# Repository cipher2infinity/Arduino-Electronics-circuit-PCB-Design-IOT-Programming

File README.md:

# Arduino : Electronics circuit, PCB Design & IOT Programming

You can check the course curriculum on our [WEBSITE](https://www.cipher2infinity.com/)

## Content
* Images of Datalogger
* Hardware design files and firmware files for Industrial DataLogger.
* Examples codes used in demos of all the sections of datalogger.
* hardware descreption section includes descreptions for all the hardware blocks of datalogger. 
* Libraries used in demo code

## Introduction
Please check the following links for demostration of Datalogger

1. This [video](https://drive.google.com/open?id=1AglGJTn_O3K_O5rFmPPeSSnq5-zFRN2F) describes the entire PCB of Industrial Datalogger

2. This [video](https://drive.google.com/open?id=1-QjOal9vDFr6C30vdyRp-lrAA95-3nSr) gives the demostration of each and every inetrface of Industrial Datalogger

## Features
* SMPS (5V)
* LDO Regulator (3.3v)
* Relay Driver										 (2 CH)
* DC Motor Speed Controller
* 0-10 V Digital Input 					 (4 CH)
* 0-10 V Analog Input 						 (4 CH)
* 4-20 mA Receiver								 (2 CH)
* Real Time Clock
* Bluetooth Low Energy 
* WiFi Module
* SD Card Module
* RS232 Interface
* RS485 Interface
* 6 Pin ICSP Headers
* Serial Programming using UART0

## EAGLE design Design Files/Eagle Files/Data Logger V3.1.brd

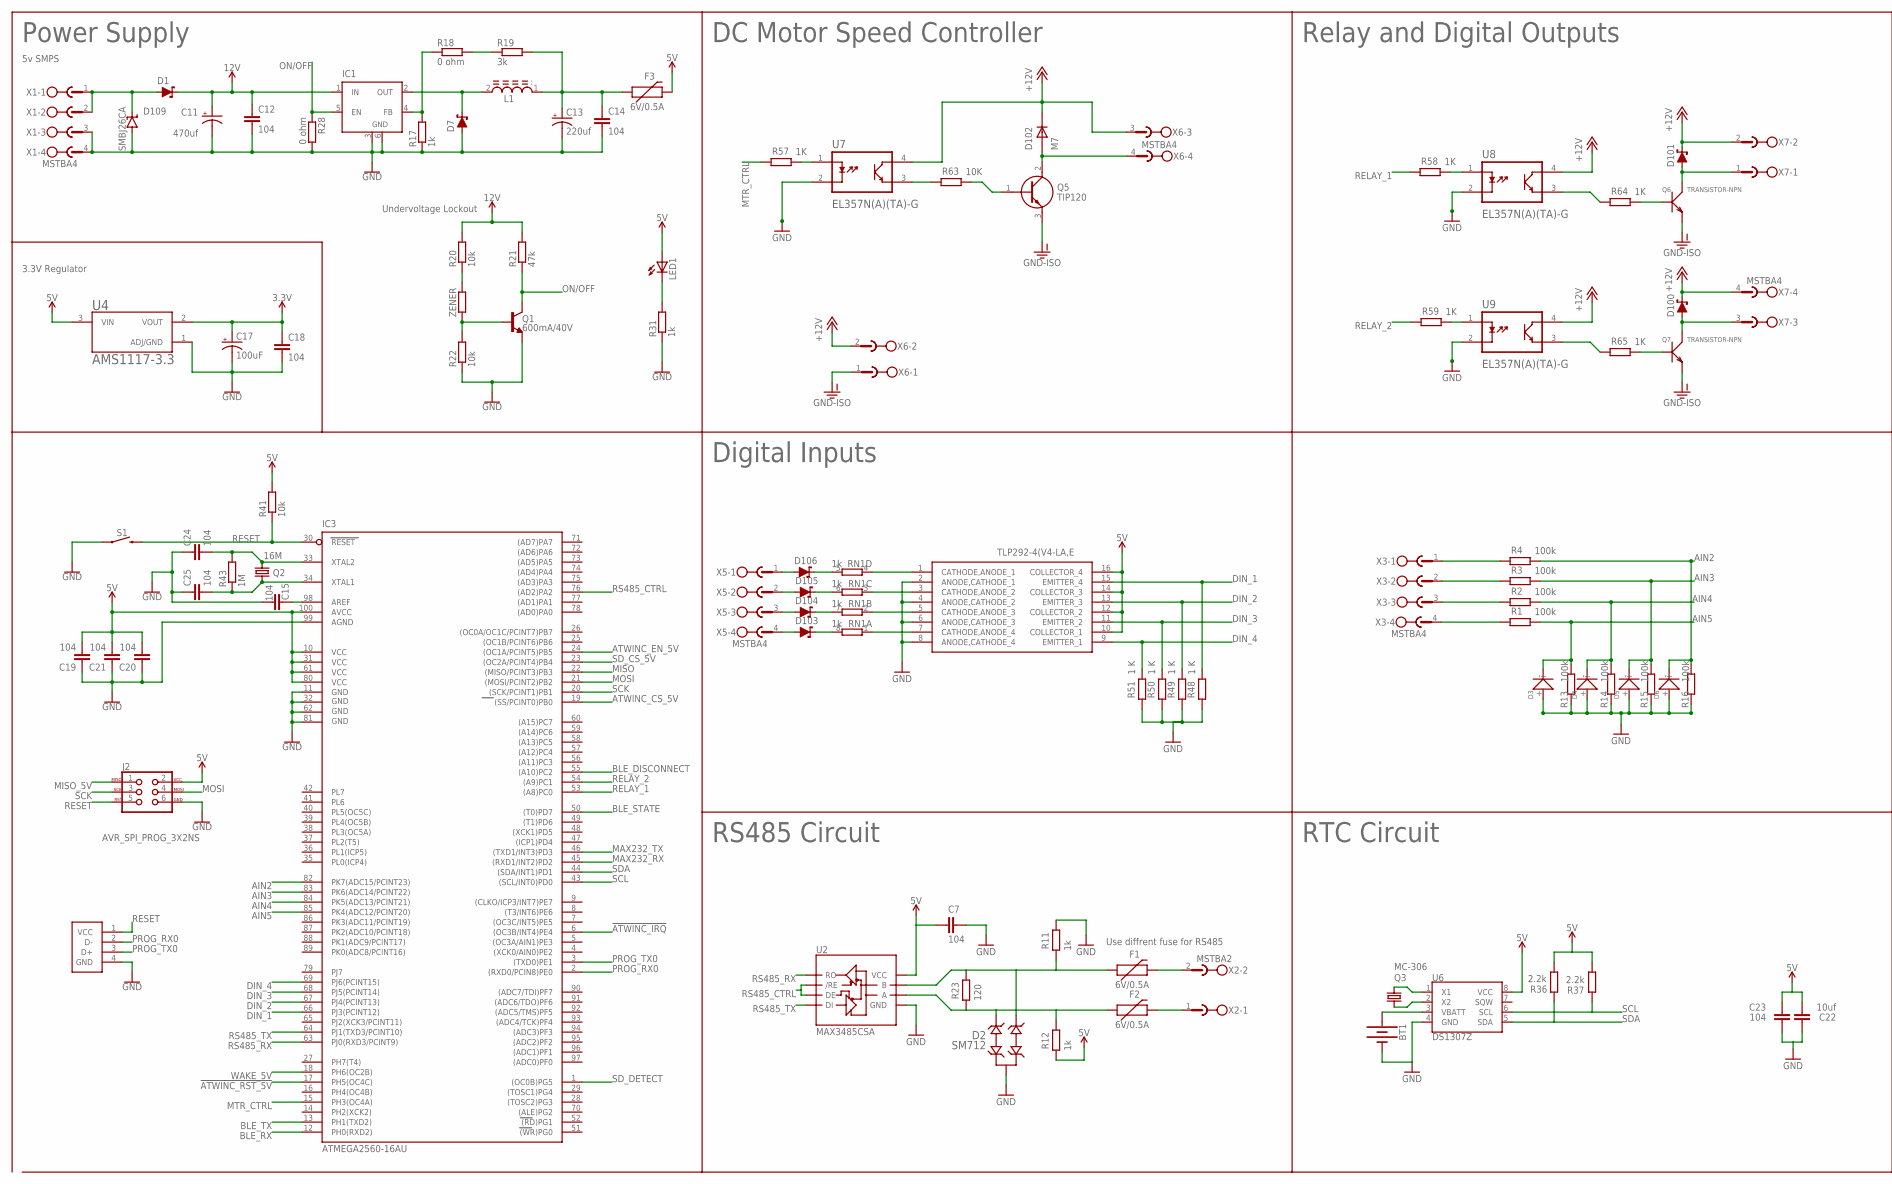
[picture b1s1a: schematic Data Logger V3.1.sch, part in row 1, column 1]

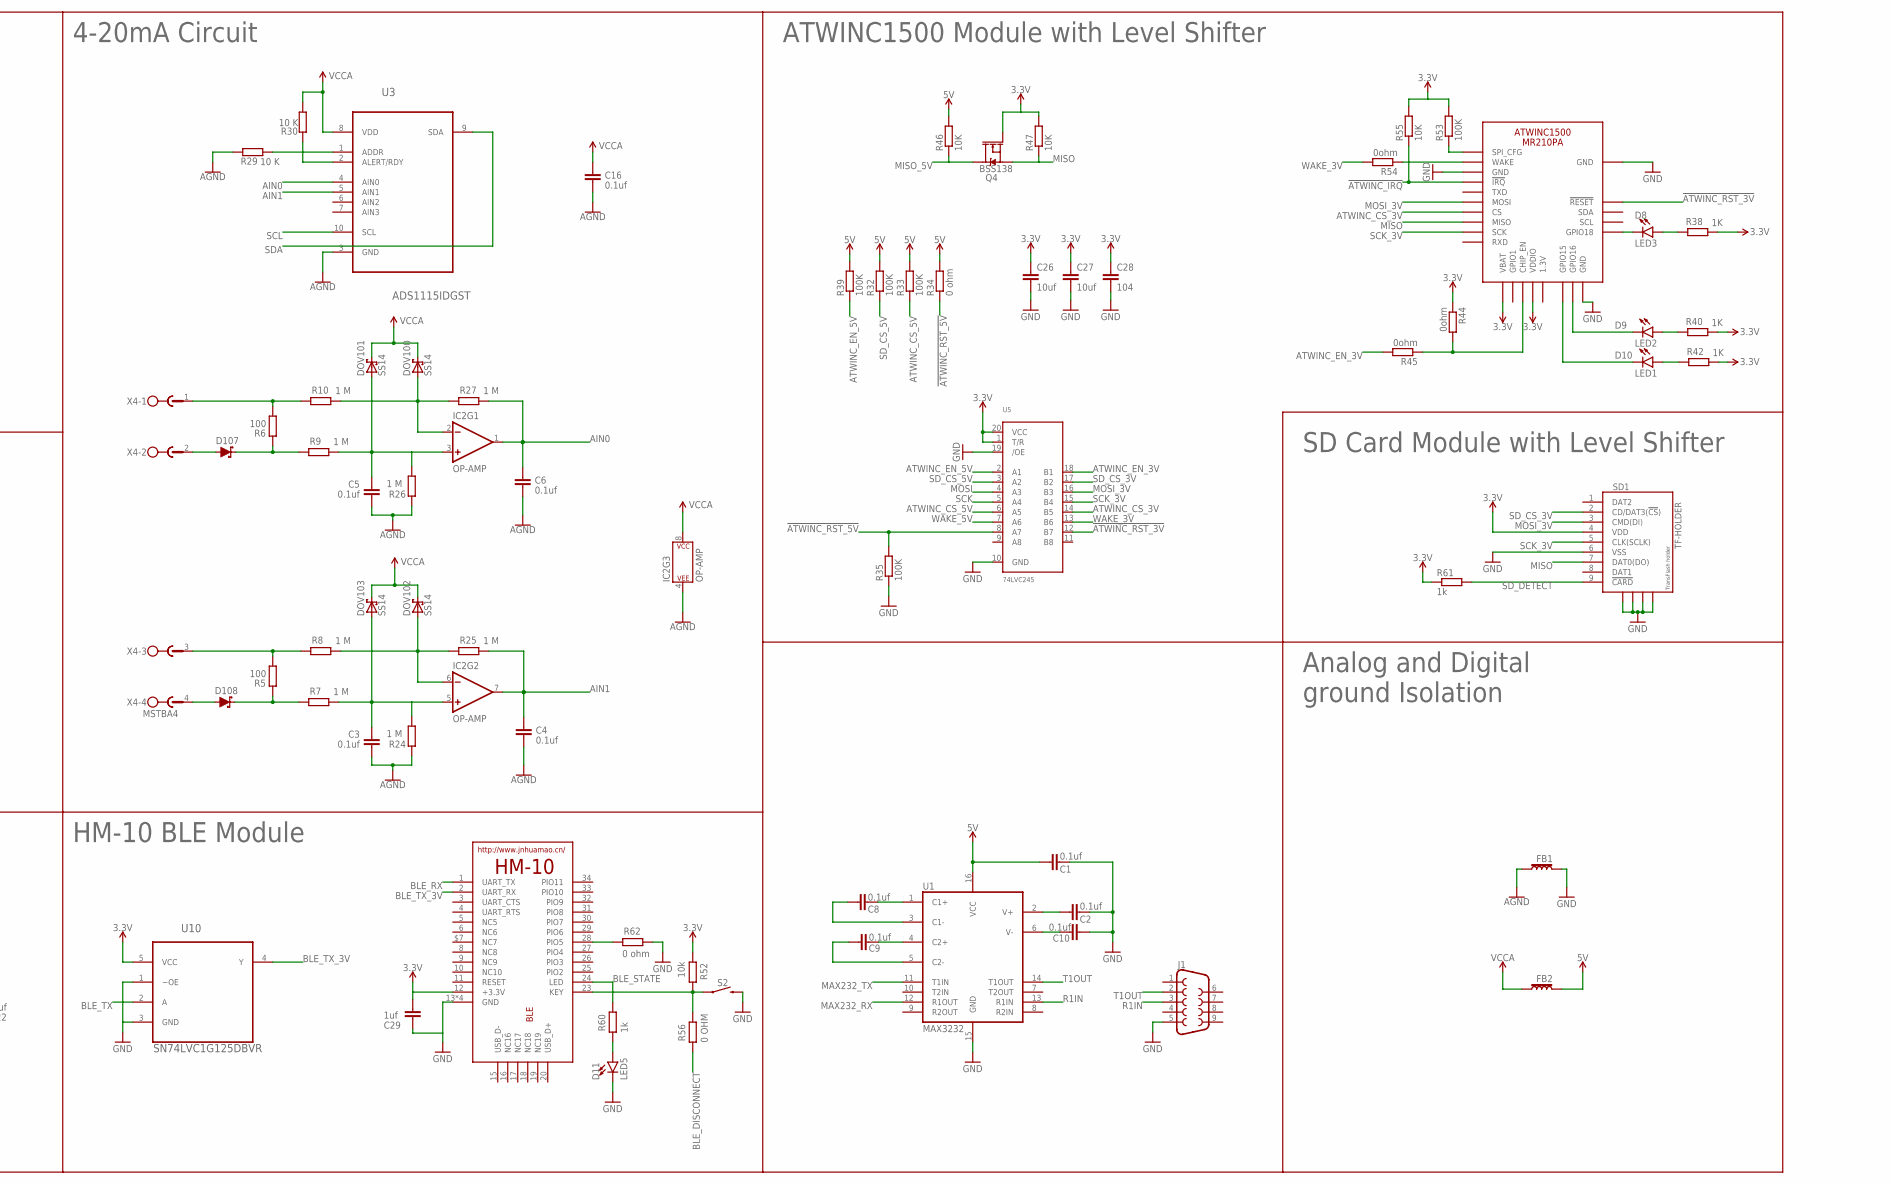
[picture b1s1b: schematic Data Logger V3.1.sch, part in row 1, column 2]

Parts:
BLE: HM-10-BOARD; 26.9X13X2.2_BOARD
BT1: BATTERY-20MM_PTH; BATTCOM_20MM_PTH
C1, C2, C3, C4, C5, C6, C8, C9, C10, C16: 0.1uf; C0805
C7, C12, C14, C15, C18, C19, C20, C21, C23, C24, C25, C28: 104; C0805
C11: 470uf; E5-8,5
C13: 220uf; 150CLZ-1014
C17: 100uF; PANASONIC_D
C22, C26, C27: 10uf; C0805
C29: 1uf; C0805
D1, D7, D100, D101, D103, D104, D105, D106, D107, D108: 3A/40V/500mV; SMA-DIODE
D2: SM712; SOT-23-3
D3, D4, D5, D6: SMD-DIODE-ZENER-5.1V-500MW(SOD-123); SOD-123
D8: LED3; LED-0603
D9: LED2; LED-0603
D10: LED1; LED-0603
D11: LED5; LED-0603
D102: M7; DIOM505270X240
D109: SMBJ26CA; SMBJ
DOV100, DOV101, DOV102, DOV103: SS14; DO-214AC
F1, F2, F3: 6V/0.5A; 1206
FB1, FB2: 30Ω/1.8A; 0603
IC1: LM2596S; TO263-5
IC2: OP-AMP; SO08
IC3: ATMEGA2560-16AU; TQFP100
IC4: TLP292-4(V4-LA,E; SOIC127P700X230-16N
J1: DB9MALE; DB9_MALE
J2: AVR_SPI_PROG_3X2NS; 2X3-NS
L1: SRR1260-680M; INDP125125X600N
LED1: LEDCHIP-LED0805; CHIP-LED0805
PROG: 61400416121
Q1: 600mA/40V; SOT23-3
Q2: 16M; HC49US
Q3: MC-306
Q4: BSS138; SOT23-3
Q5: TIP120; TO220
Q6, Q7: TRANSISTOR-NPN; SOT-23
R1, R2, R3, R4, R13, R14, R15, R16: 100k; R0805
R5, R6: 100; R0805
R7, R8, R9, R10, R24, R25, R26, R27: 1 M; R0805
R11, R12, R17, R31, R60, R61: 1k; R0805
R18, R28, R34, R62: 0 ohm; R0805
R19: 3k; R0805
R20, R22, R41, R52: 10k; R0805
R21: 47k; R0805
R23: 120; R0805
R29, R30: 10 K; R0805
R32, R33, R35, R39, R53: 100K; R0805
R36, R37: 2.2k; R0805
R38, R40, R42, R57, R58, R59, R64, R65: 1K; R0805
R43: 1M; R0805
R44, R45, R54: 0ohm; R0805
R46, R47, R55, R63: 10K; R0805
R48, R49, R50, R51: 1 K; R0805
R56: 0 OHM; R0805
RN1: 1k; CAY16
S1, S2: MOMENTARY-SWITCH-SPST-SMD-6.0X3.5MM; TACTILE_SWITCH_SMD_6.0X3.5MM
SD1: TF-HOLDER; TF-PULL
U1: MAX3232; SO16
U2: MAX3485CSA; SO08
U3: ADS1115IDGST; SOP50P490X110-10N
U4: AMS1117-3.3; SOT229P700X180-4N
U5: 74LVC245; TSSOP20
U6: DS1307Z; SO08-0.15
U7, U8, U9: EL357N(A)(TA)-G; SOP254P700X200-4N
U10: SN74LVC1G125DBVR; SOT95P280X145-5N
WIFI: ATWINC1500_MR210PB; ATWINC1500_MR210PA
X1, X3, X4, X5, X6, X7: MSTBA4
X2: MSTBA2
ZENER: R0204/7; 0204/7

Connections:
3.3V: BLE.12 (+3.3V), C17.+, C18.1, C26.1, C27.1, C28.1, C29.2, Q4.1 (G), R38.1, R40.1, R42.1, R44.1, R47.2, R52.2, R53.2, R55.2, R61.1, SD1.4 (VDD), U4.2 (VOUT), U5.1 (T/R), U5.20 (VCC), U10.5 (VCC), WIFI.J20 (VBAT), WIFI.J23 (VDDIO)
5V: C1.2, C7.1, C19.2, C20.2, C21.2, C22.2, C23.2, F3.2, FB2.2, IC3.10 (VCC), IC3.31 (VCC1), IC3.61 (VCC2), IC3.80 (VCC3), IC3.100 (AVCC), IC4.10 (COLLECTOR_1), IC4.12 (COLLECTOR_2), IC4.14 (COLLECTOR_3), IC4.16 (COLLECTOR_4), J2.2, LED1.A, R12.2, R32.2, R33.2, R34.2, R36.1, R37.1, R39.2, R41.2, R46.2, U1.16 (VCC), U2.8 (VCC), U4.3 (VIN), U6.8 (VCC)
12V: C11.+, C12.1, D1.C, IC1.1 (IN), R20.2, R21.2
!ATWINC_IRQ: IC3.6 ((OC3B/INT4)PE4), R55.1, WIFI.J13 (!IRQ)
!ATWINC_RST_3V: U5.12 (B7), WIFI.J4 (!RESET)
!ATWINC_RST_5V: IC3.17 (PH5(OC4C)), R34.1, R35.2, U5.8 (A7)
+12V: D100.C, D101.C, D102.C, U7.4 (C), U8.4 (C), U9.4 (C), X6.2, X6.3, X7.2, X7.4
AGND: C3.1, C4.1, C5.1, C6.1, C16.1, FB1.1, IC2.4 (P$V-), R24.2, R26.2, R29.1, U3.3 (GND)
AIN0: C6.2, IC2.1 (OUT), R27.1, U3.4 (AIN0)
AIN1: C4.2, IC2.7 (OUT), R25.1, U3.5 (AIN1)
AIN2: D6.-, IC3.82 (PK7(ADC15/PCINT23)), R4.1, R16.1
AIN3: D5.-, IC3.83 (PK6(ADC14/PCINT22)), R3.1, R15.1
AIN4: D4.-, IC3.84 (PK5(ADC13/PCINT21)), R2.1, R14.1
AIN5: D3.-, IC3.85 (PK4(ADC12/PCINT20)), R1.1, R13.1
AREF: C15.1, IC3.98 (AREF)
ATWINC_CS_3V: U5.14 (B5), WIFI.J16 (CS)
ATWINC_CS_5V: IC3.19 ((SS/PCINT0)PB0), R33.1, U5.6 (A5)
ATWINC_EN_3V: R45.2, U5.18 (B1)
ATWINC_EN_5V: IC3.24 ((OC1A/PCINT5)PB5), R39.1, U5.2 (A1)
BLE_DISCONNECT: IC3.55 ((A10)PC2), R56.2
BLE_RX: BLE.1 (UART_TX), IC3.12 (PH0(RXD2))
BLE_STATE: BLE.24 (LED), IC3.50 ((T0)PD7), R60.1
BLE_TX: IC3.13 (PH1(TXD2)), U10.2 (A)
BLE_TX_3V: BLE.2 (UART_RX), U10.4 (Y)
DIN_1: IC3.66 (PJ3(PCINT12)), IC4.15 (EMITTER_4), R48.1
DIN_2: IC3.67 (PJ4(PCINT13)), IC4.13 (EMITTER_3), R49.1
DIN_3: IC3.68 (PJ5(PCINT14)), IC4.11 (EMITTER_2), R50.1
DIN_4: IC3.69 (PJ6(PCINT15)), IC4.9 (EMITTER_1), R51.1
GND: BLE.13 (GND), BLE.14 (GND), BLE.21 (GND), BLE.22 (GND), BT1.2 (-), C1.1, C2.1, C7.2, C10.1, C11.-, C12.2, C13.-, C14.2, C15.2, C17.-, C18.2, C19.1, C20.1, C21.1, C22.1, C23.1, C24.1, C25.1, C26.2, C27.2, C28.2, C29.1, D2.3 (GND), D3.+, D4.+, D5.+, D6.+, D7.A, D11.C, D109.A, FB1.2, IC1.3 (GND), IC1.6 (GND), IC3.11 (GND), IC3.32 (GND1), IC3.62 (GND2), IC3.81 (GND3), IC3.99 (AGND), IC4.2 (ANODE,CATHODE_1), IC4.4 (ANODE,CATHODE_2), IC4.6 (ANODE,CATHODE_3), IC4.8 (ANODE,CATHODE_4), J1.5, J2.6, PROG.4 (GND), Q1.2 (E), R11.1, R13.2, R14.2, R15.2, R16.2, R17.1, R22.1, R28.2, R31.1, R35.1, R48.2, R49.2, R50.2, R51.2, R62.1, S1.1, S2.2, SD1.6 (VSS), SD1.S1, SD1.S2, SD1.S3, SD1.S4, U1.15 (GND), U2.5 (GND), U4.1 (ADJ/GND), U5.10 (GND), U5.19 (/OE), U6.4 (GND), U7.2 (K), U8.2 (K), U9.2 (K), U10.1 (~OE), U10.3 (GND), WIFI.J9 (GND), WIFI.J12 (GND), WIFI.J28 (GND), WIFI.MTGND (GND), X1.3, X1.4
GND-ISO: Q5.3 (E), Q6.2 (E), Q7.2 (E), X6.1
MAX232_RX: IC3.45 ((RXD1/INT2)PD2), U1.12 (R1OUT)
MAX232_TX: IC3.46 ((TXD1/INT3)PD3), U1.11 (T1IN)
MISO: IC3.22 ((MISO/PCINT3)PB3), Q4.2 (S), R47.1, SD1.7 (DAT0(DO)), WIFI.J17 (MISO)
MISO_5V: J2.1, Q4.3 (D), R46.1
MOSI: IC3.21 ((MOSI/PCINT2)PB2), J2.4, U5.4 (A3)
MOSI_3V: SD1.3 (CMD(DI)), U5.16 (B3), WIFI.J15 (MOSI)
MTR_CTRL: IC3.15 (PH3(OC4A)), R57.2
unnamed: C13.+, C14.1, F3.1, L1.1, R19.2
unnamed: D8.C, WIFI.J1 (GPIO18)
unnamed: R58.1, U8.1 (A)
unnamed: R4.2, X3.1
unnamed: D9.C, WIFI.J27 (GPIO16)
unnamed: D10.C, WIFI.J26 (GPIO15)
unnamed: R53.1, WIFI.J10 (SPI_CFG)
unnamed: D10.A, R42.2
unnamed: D9.A, R40.2
unnamed: D8.A, R38.2
unnamed: D2.2 (IO2), F1.1, R11.2, R23.1, U2.7 (B)
unnamed: D2.1 (IO1), F2.1, R12.1, R23.2, U2.6 (A)
unnamed: R3.2, X3.2
unnamed: BT1.1 (+), U6.3 (VBATT)
unnamed: F1.2, X2.2
unnamed: F2.2, X2.1
unnamed: Q3.1, U6.1 (X1)
unnamed: Q3.4 (2), U6.2 (X2)
unnamed: BLE.28 (PIO5), R62.2
unnamed: R2.2, X3.3
unnamed: R59.1, U9.1 (A)
unnamed: R1.2, X3.4
unnamed: R44.2, R45.1, WIFI.J22 (CHIP_EN)
unnamed: R54.1, WIFI.J11 (WAKE)
unnamed: BLE.23 (KEY), R52.1, R56.1, S2.1
unnamed: R30.1, U3.2 (ALERT/RDY)
unnamed: R29.2, U3.1 (ADDR)
unnamed: C5.2, DOV101.A, IC2.3 (+IN), R9.1, R26.1
unnamed: R63.2, U7.3 (E)
unnamed: DOV100.A, IC2.2 (-IN), R10.1, R27.2
unnamed: R6.1, R10.2, X4.1
unnamed: D11.A, R60.2
unnamed: D108.A, X4.4
unnamed: Q5.1 (B), R63.1
unnamed: R64.2, U8.3 (E)
unnamed: D108.C, R5.2, R7.2
unnamed: D107.A, X4.2
unnamed: D103.A, X5.4
unnamed: D103.C, RN1.8 (2)
unnamed: D104.C, RN1.7 (2)
unnamed: D104.A, X5.3
unnamed: D105.A, X5.2
unnamed: C3.2, DOV103.A, IC2.5 (+IN), R7.1, R24.1
unnamed: DOV102.A, IC2.6 (-IN), R8.1, R25.2
unnamed: D105.C, RN1.6 (2)
unnamed: D107.C, R6.2, R9.2
unnamed: R65.2, U9.3 (E)
unnamed: R5.1, R8.2, X4.3
unnamed: D106.C, RN1.5 (2)
unnamed: D106.A, X5.1
unnamed: R20.1, ZENER.2
unnamed: R57.1, U7.1 (A)
unnamed: D102.A, Q5.2 (C), X6.4
unnamed: D7.C, IC1.2 (OUT), L1.2
unnamed: D1.A, D109.C, X1.1, X1.2
unnamed: IC1.4 (FB), R17.2, R18.1
unnamed: R18.2, R19.1
unnamed: Q1.1 (B), R22.2, ZENER.1
unnamed: LED1.C, R31.2
unnamed: C24.2, IC3.33 (XTAL2), Q2.2, R43.2
unnamed: C25.2, IC3.34 (XTAL1), Q2.1, R43.1
unnamed: IC4.1 (CATHODE,ANODE_1), RN1.4 (1)
unnamed: IC4.3 (CATHODE,ANODE_2), RN1.3 (1)
unnamed: IC4.5 (CATHODE,ANODE_3), RN1.2 (1)
unnamed: IC4.7 (CATHODE,ANODE_4), RN1.1
unnamed: C8.2, U1.1 (C1+)
unnamed: C8.1, U1.3 (C1-)
unnamed: C9.1, U1.4 (C2+)
unnamed: C9.2, U1.5 (C2-)
unnamed: C2.2, U1.2 (V+)
unnamed: C10.2, U1.6 (V-)
unnamed: Q6.1 (B), R64.1
unnamed: Q7.1 (B), R65.1
unnamed: D100.A, Q7.3 (C), X7.3
unnamed: D101.A, Q6.3 (C), X7.1
ON/OFF: IC1.5 (EN), Q1.3 (C), R21.1, R28.1
PROG_RX0: IC3.2 ((RXD0/PCIN8)PE0), PROG.2 (D-)
PROG_TX0: IC3.3 ((TXD0)PE1), PROG.3 (D+)
R1IN: J1.3, U1.13 (R1IN)
RELAY_1: IC3.53 ((A8)PC0), R58.2
RELAY_2: IC3.54 ((A9)PC1), R59.2
RESET: IC3.30 (RESET), J2.5, PROG.1 (VCC), R41.1, S1.2
RS485_CTRL: IC3.76 ((AD2)PA2), U2.2 (/RE), U2.3 (DE)
RS485_RX: IC3.63 (PJ0(RXD3/PCINT9)), U2.1 (RO)
RS485_TX: IC3.64 (PJ1(TXD3/PCINT10)), U2.4 (DI)
SCK: IC3.20 ((SCK/PCINT1)PB1), J2.3, U5.5 (A4)
SCK_3V: SD1.5 (CLK(SCLK)), U5.15 (B4), WIFI.J18 (SCK)
SCL: IC3.43 ((SCL/INT0)PD0), R37.2, U3.10 (SCL), U6.6 (SCL)
SDA: IC3.44 ((SDA/INT1)PD1), R36.2, U3.9 (SDA), U6.5 (SDA)
SD_CS_3V: SD1.2 (CD/DAT3(!CS!)), U5.17 (B2)
SD_CS_5V: IC3.23 ((OC2A/PCINT4)PB4), R32.1, U5.3 (A2)
SD_DETECT: IC3.1 ((OC0B)PG5), R61.2, SD1.9 (!CARD)
T1OUT: J1.2, U1.14 (T1OUT)
VCCA: C16.2, DOV100.C, DOV101.C, DOV102.C, DOV103.C, FB2.1, IC2.8 (P$V+), R30.2, U3.8 (VDD)
WAKE_3V: R54.2, U5.13 (B6)
WAKE_5V: IC3.18 (PH6(OC2B)), U5.7 (A6)

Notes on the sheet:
3.3V Regulator
Power Supply
Undervoltage Lockout
5v SMPS
SD Card Module with Level Shifter
ATWINC1500 Module with Level Shifter
RS485 Circuit
RTC Circuit
Analog and Digital ground Isolation
Use diffrent fuse for RS485
Relay and Digital Outputs
Digital Inputs
4-20mA Circuit
HM-10 BLE Module
DC Motor Speed Controller

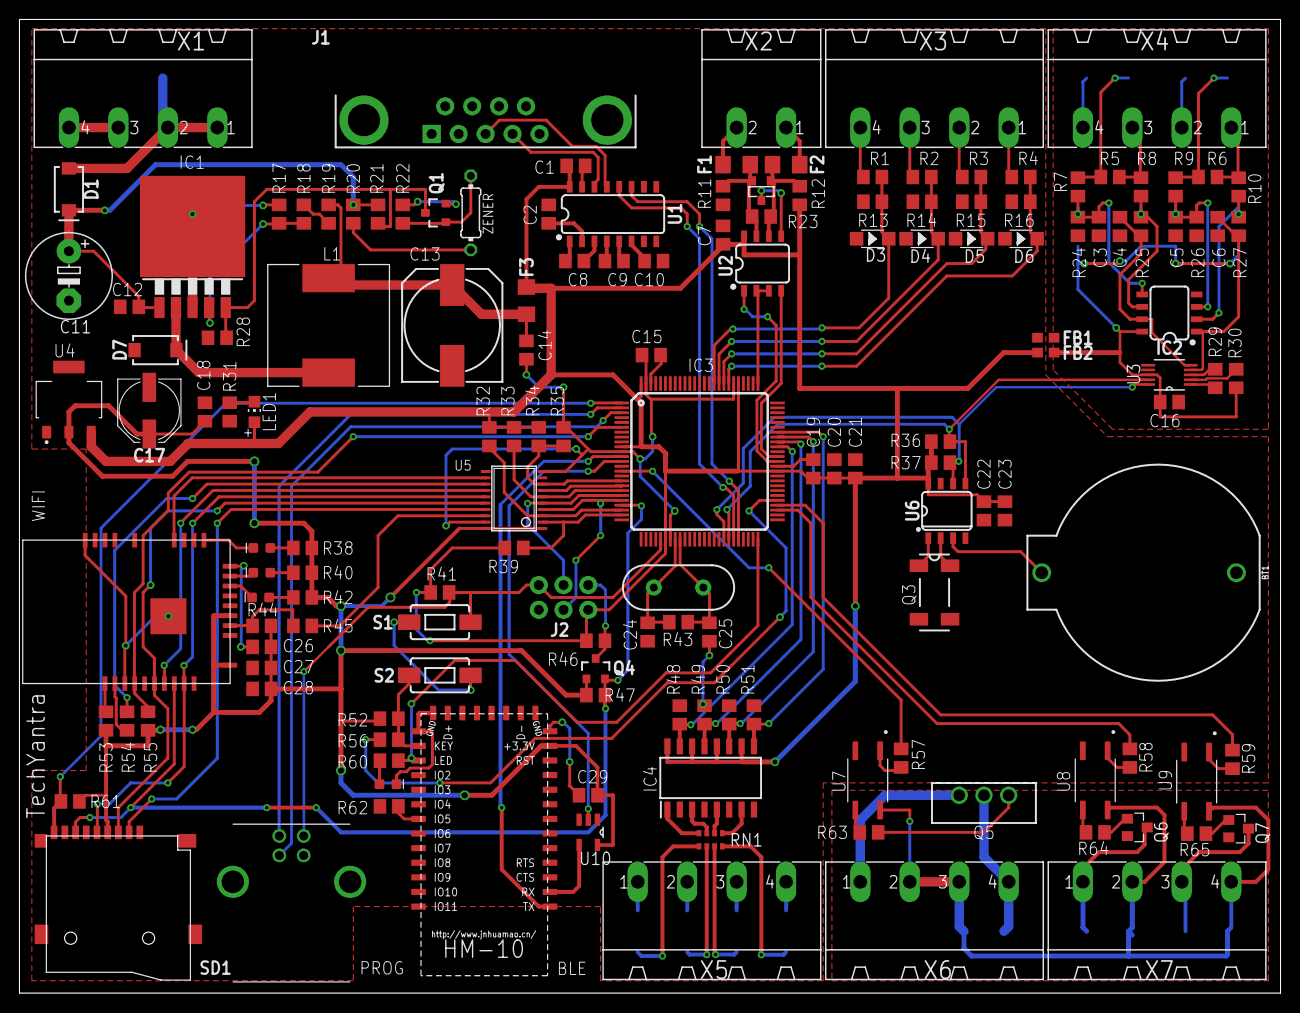
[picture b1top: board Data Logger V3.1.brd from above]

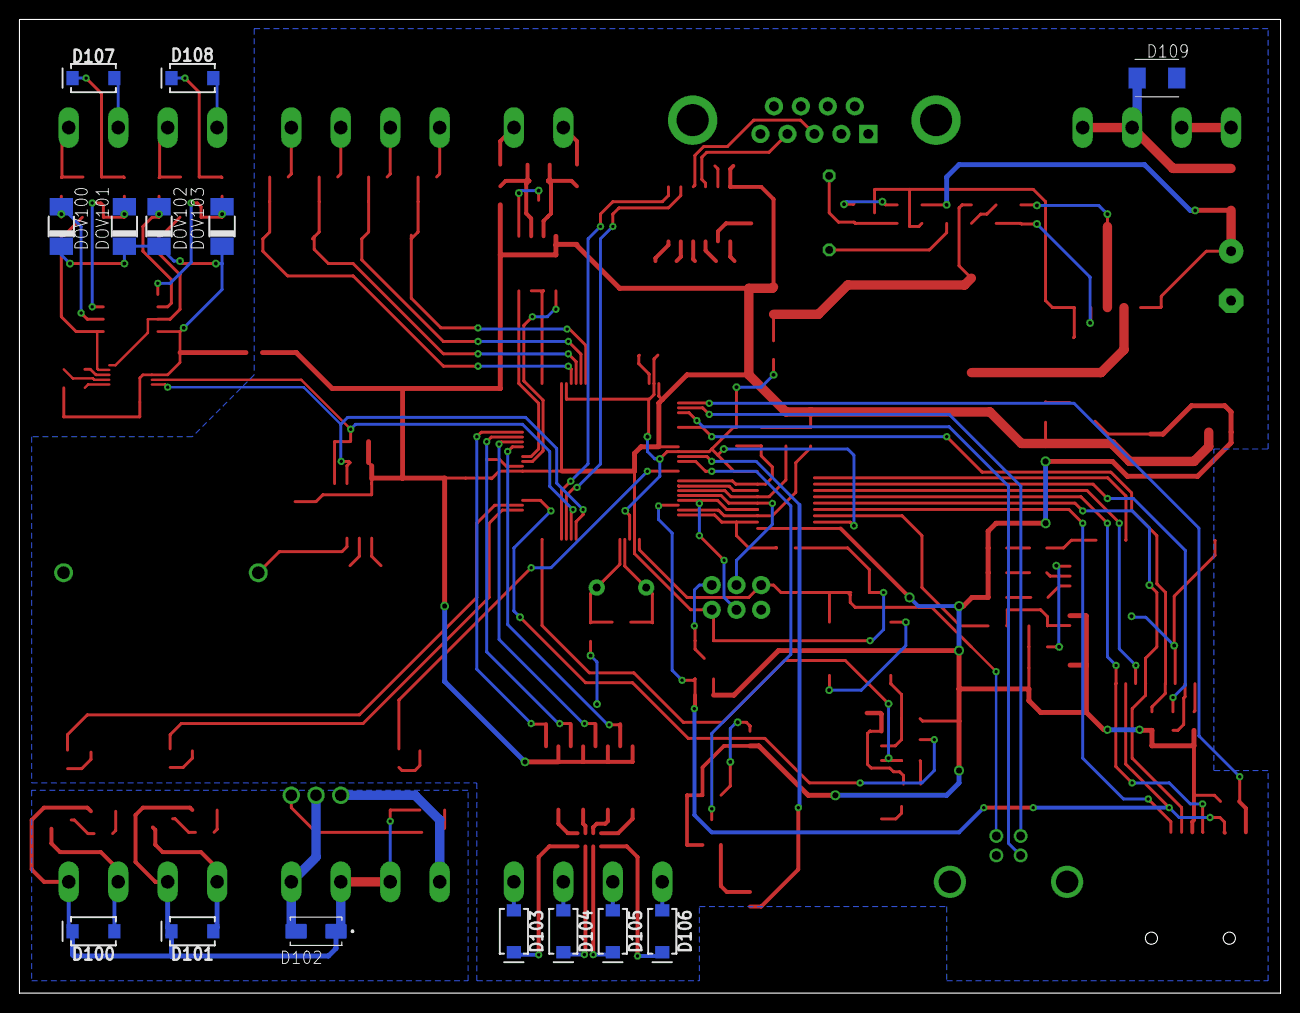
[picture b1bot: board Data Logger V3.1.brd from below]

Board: 2 copper layers, 129.5 x 100.0 mm, 165 parts (14 on the bottom side), 133 nets.

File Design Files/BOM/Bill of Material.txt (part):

Partlist exported from E:/Projects/Data Logger V3.0/Data Logger V3.0/Data Logger V3.1.sch at 6/3/2019 9:30 AM

Part   Value                               Device                              Package                      Description                                                                                                                                                                                                                                       AVAILABILITY DESCRIPTION                                                                                      HEIGHT MANUFACTURER_NAME       MANUFACTURER_PART_NUMBER MF                          MOUSER_PART_NUMBER MOUSER_PRICE-STOCK                                                   MP               MPN                            OC_FARNELL OC_NEWARK PACKAGE                          PRICE PROD_ID     RS_PART_NUMBER RS_PRICE-STOCK                                               SF_SKU    SPICEMODEL SPICEPREFIX VALUE        
BLE    HM-10-BOARD                         HM-10-BOARD                         26.9X13X2.2_BOARD            HM Bluetooth module use TI CC2540 or CC2541, Master and slave roles in one, transmission version and remote control version and PIO state acquisition functions in one, Support the AT command modify module parameters, Convenient and flexible.                                                                                                                                                                                                                                                                                                                                                                                                                                                                                                                                             
BT1                                        BATTERY-20MM_PTH                    BATTCOM_20MM_PTH             Battery - Single Cell                                                                                                                                                                                                                                                                                                                                                                                                                                                                                                                                                                                                                                   BATT-09031                                                                              PRT-00783                                     
C1     0.1uf                               C-EUC0805                           C0805                        CAPACITOR, European symbol                                                                                                                                                                                                                                                                                                                                                                                                                                                                                                                                                                                                                                                                                                                                           C                        
C2     0.1uf                               C-EUC0805                           C0805                        CAPACITOR, European symbol                                                                                                                                                                                                                                                                                                                                                                                                                                                                                                                                                                                                                                                                                                                                           C                        
C3     0.1uf                               C-EUC0805                           C0805                        CAPACITOR, European symbol                                                                                                                                                                                                                                                                                                                                                                                                                                                                                                                                                                                                                                                                                                                                           C                        
C4     0.1uf                               C-EUC0805                           C0805                        CAPACITOR, European symbol                                                                                                                                                                                                                                                                                                                                                                                                                                                                                                                                                                                                                                                                                                                                           C                        
C5     0.1uf                               C-EUC0805                           C0805                        CAPACITOR, European symbol                                                                                                                                                                                                                                                                                                                                                                                                                                                                                                                                                                                                                                                                                                                                           C                        
C6     0.1uf                               C-EUC0805                           C0805                        CAPACITOR, European symbol                                                                                                                                                                                                                                                                                                                                                                                                                                                                                                                                                                                                                                                                                                                                           C                        
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
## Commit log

2019-06-06 Create Images
2019-06-06 Create f
2019-06-06 Rename f to file
2019-06-06 Create design
2019-06-06 Create gerber
2019-06-06 Create gerber file
2019-06-06 Create drill
2019-06-06 Create m
2019-06-06 Create r
2019-06-06 Create b
2019-06-06 Create n
2019-06-06 Create g
2019-06-06 Create h
2019-06-06 Create k
2019-06-06 Create j
2019-06-06 Create L
2019-06-06 Create D
2019-06-06 Create a
2019-06-06 Create 2. Atmega256 Circuit
2019-06-06 Create s
2019-06-06 Create w
2019-06-06 Create o
2019-06-06 Create p
2019-06-06 Create t
2019-06-06 Create y
2019-06-06 Create u
2019-06-06 Update y
2019-06-06 Create Power Supply Descreption
2019-06-06 Update Power Supply Descreption
2019-08-31 Create Additional Parts
2019-08-31 Update Additional Parts
2019-09-30 Create main

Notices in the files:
parts and their libraries:
SparkFun-Batteries: Licensing: Creative Commons ShareAlike 4.0 International - https://creativecommons.org/licenses/by-sa/4.0
Wuerth_Elektronik_eiCan_Communication_Co: Copyright: Würth Elektronik
